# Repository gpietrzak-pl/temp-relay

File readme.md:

Program sterujący przekaźnikiem mechanicznym w zależności od aktualnej temperatury. Ma służyć do sterowania wentylatorem gdy wykryje, że piec robi się ciepły, po wygaśnięciu wyłącza wentylator.

możliwość zmiany temperatury od 20st z krokiem co 5 st do 55 stopni (DHT11 i tak tylko do 50st działa)

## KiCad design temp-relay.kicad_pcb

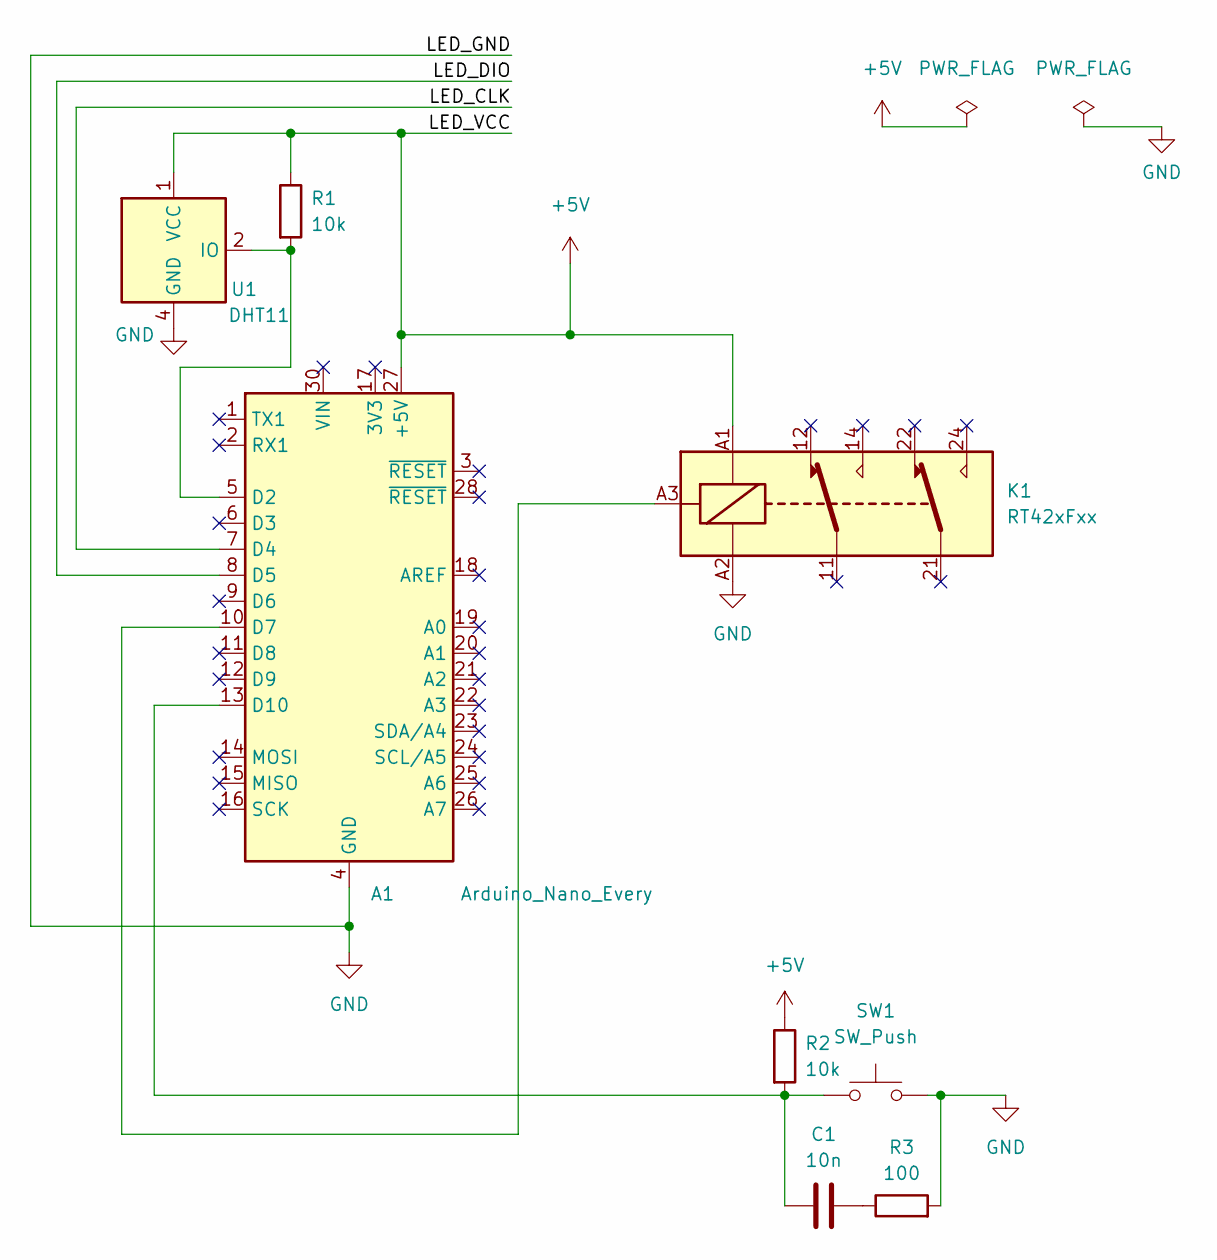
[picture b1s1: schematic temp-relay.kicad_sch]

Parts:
A1: Arduino_Nano_Every; Arduino_Nano
C1: 10n; CP_Axial_L10.0mm_D4.5mm_P15.00mm_Horizontal
K1: RT42xFxx; Relay_DPDT_Schrack-RT2-FormC-Dual-Coil_RM5mm
R1, R2: 10k; R_Axial_DIN0204_L3.6mm_D1.6mm_P5.08mm_Horizontal
R3: 100; R_Axial_DIN0204_L3.6mm_D1.6mm_P5.08mm_Horizontal
SW1: SW_Push; R_Axial_DIN0204_L3.6mm_D1.6mm_P5.08mm_Horizontal
U1: DHT11; Aosong_DHT11_5.5x12.0_P2.54mm

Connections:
+5V: A1.27 (+5V), K1.A1, R1.1, R2.1, U1.1 (VCC)
/LED_CLK: A1.7 (D4)
/LED_DIO: A1.8 (D5)
GND: A1.4 (GND), A1.29 (GND), K1.A2, R3.2, SW1.2, U1.4 (GND)
unnamed: A1.5 (D2), R1.2, U1.2 (IO)
unnamed: A1.10 (D7), K1.A3
unnamed: A1.13 (D10), C1.1, R2.2, SW1.1
unnamed: C1.2, R3.1

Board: 2 copper layers, 8 parts (0 on the bottom side), 6 nets, no tracks yet.

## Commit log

2022-10-15 1st ver
2022-10-15 add to .gitignore: backup files
2022-10-15 Update main.arduino.ino
    Added GH address
2022-10-15 pcb update
